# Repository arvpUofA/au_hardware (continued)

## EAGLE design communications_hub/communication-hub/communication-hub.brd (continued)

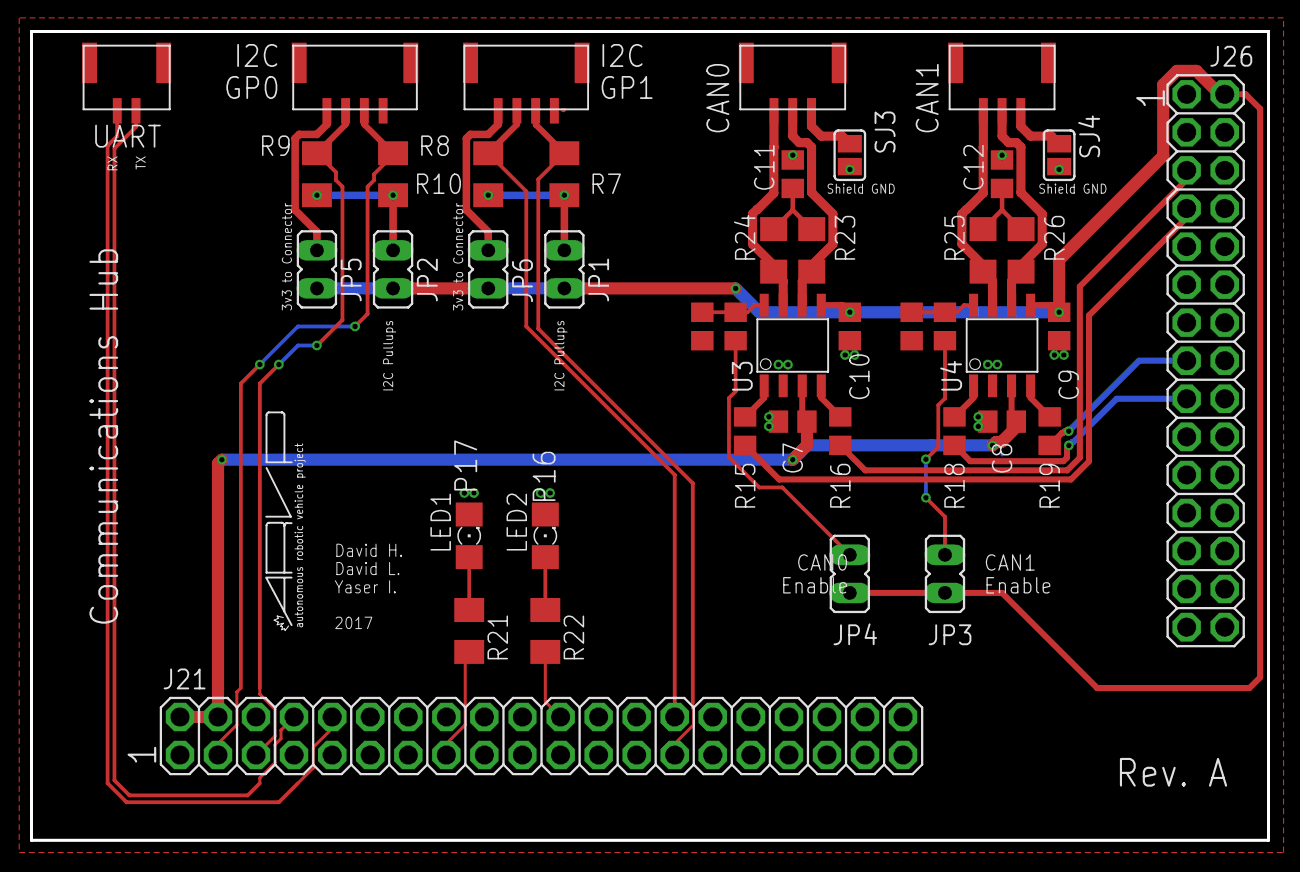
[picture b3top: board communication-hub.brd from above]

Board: 2 copper layers, 82.5 x 54.0 mm, 46 parts (0 on the bottom side), 37 nets.

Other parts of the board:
U$1: ARVP
U$2: LETTER_P
U$3: DOCFIELD

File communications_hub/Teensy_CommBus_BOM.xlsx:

Shematic Reference Number | Part Description | Manufacturer Part Number | Datasheet | Price | Quantity | Total Cost
 | RES SMD 10K OHM 1% 1/8W 0805 | RC0805FR-0710KL | http://www.yageo.com/documents/recent/PYu-RC_Group_51_RoHS_L_7.pdf | 0.047 | 6 | 0.282
 | RES SMD 220 OHM 1% 1/8W 0805 | RC0805FR-07220RL | http://www.yageo.com/documents/recent/PYu-RC_Group_51_RoHS_L_7.pdf | 0.031 | 6 | 0.186
 | RES SMD 1K OHM 1% 1/8W 0805 | RC0805FR-071KL | http://www.yageo.com/documents/recent/PYu-RC_Group_51_RoHS_L_7.pdf | 0.034 | 2 | 0.068
 | CAP CER 0.1UF 50V Y5V 0805 | CL21F104ZBCNNNC | http://www.samsungsem.com/kr/support/product-search/mlcc/CL2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 | 0.15 | 4 | 0.6
 | IC TXRX CAN 8SOIC | MCP2562-E/SN | http://ww1.microchip.com/downloads/en/DeviceDoc/20005284A.pdf | 1.42 | 2 | 2.84
 | CONN HEADER 2POS 4.2MM VERT TIN | 39281023 | http://www.molex.com/pdm_docs/sd/039281023_sd.pdf | 0.83 | 1 | 0.83
 | SIL VERTICAL PC TAIL PIN HEADER 1x2 | M20-9990245 | https://cdn.harwin.com/pdfs/M20-999.pdf | 0.2 | 1 | 0.2
 | CONN JUMPER SHORTING GOLD FLASH | SPC02SYAN | https://www.digikey.ca/products/en?keywords=SPC02SYAN | 0.15 | 4 | 0.6
 | MOSFET N-CH 50V 300MA SOT23-3 | DMN5L06K-7 | https://www.digikey.ca/product-detail/en/diodes-incorporated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 | 0.57 | 2 | 1.14
 | LED RED CLEAR 640NM SMD | XZM2MR55W-3 | https://www.digikey.ca/product-detail/en/sunled/XZM2MR55W-3/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 | 0.62 | 3 | 1.86
 | LED YELLOW CLEAR 1206 SMD | XZMYK55W-3 | https://www.digikey.ca/product-detail/en/sunled/XZMYK55W-3/1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 | 0.5 | 1 | 0.5
 | CONN RCPT .100" 40POS DUAL TIN | SSQ-120-03-T-D | https://www.digikey.ca/product-detail/en/sunled/XZMYK55W-3/1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 | 6.2 | 1 | 6.2
 | CONN RCPT .100" 30POS DUAL TIN | SSQ-115-03-T-D | https://www.digikey.ca/product-detail/en/sunled/XZMYK55W-3/1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 | 5.15 | 1 | 5.15
 | RES SMD 62 OHM 1% 1/4W 1206 | 311-62ERCT-ND | https://www.digikey.ca/product-detail/en/samsung-electro-mec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 | 0.15 | 4 | 0.6
 | CONN HEADER GH SIDE 4POS 1.25MM | SM04B-GHS-TB(LF)(SN)- | https://www.digikey.ca/product-detail/en/jst-sales-america-i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 | 0.45 | 4 | 1.8
 | CONN HEADER GH SIDE 2POS 1.25MM | SM02B-GHS-TB(LF)(SN) | https://www.digikey.ca/product-detail/en/jst-sales-america-i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 | 0.46 | 1 | 0.46
 | RES SMD 68 OHM 1% 1/8W 0805 | RC0805FR-0768RL | http://www.yageo.com/documents/recent/PYu-RC_Group_51_RoHS_L_9.pdf | 0.15 | 2 | 0.3
 | RES SMD 140 OHM 1% 1/8W 0805 | RC0805FR-07140RL | http://www.yageo.com/documents/recent/PYu-RC_Group_51_RoHS_L_9.pdf | 0.15 | 2 | 0.3
 | TVS DIODE 24V 44V SOT23-3 | NUP2105LT1G | http://www.onsemi.com/pub/Collateral/NUP2105L-D.PDF | 0.68 | 2
Total |  |  |  |  |  | 23.916
